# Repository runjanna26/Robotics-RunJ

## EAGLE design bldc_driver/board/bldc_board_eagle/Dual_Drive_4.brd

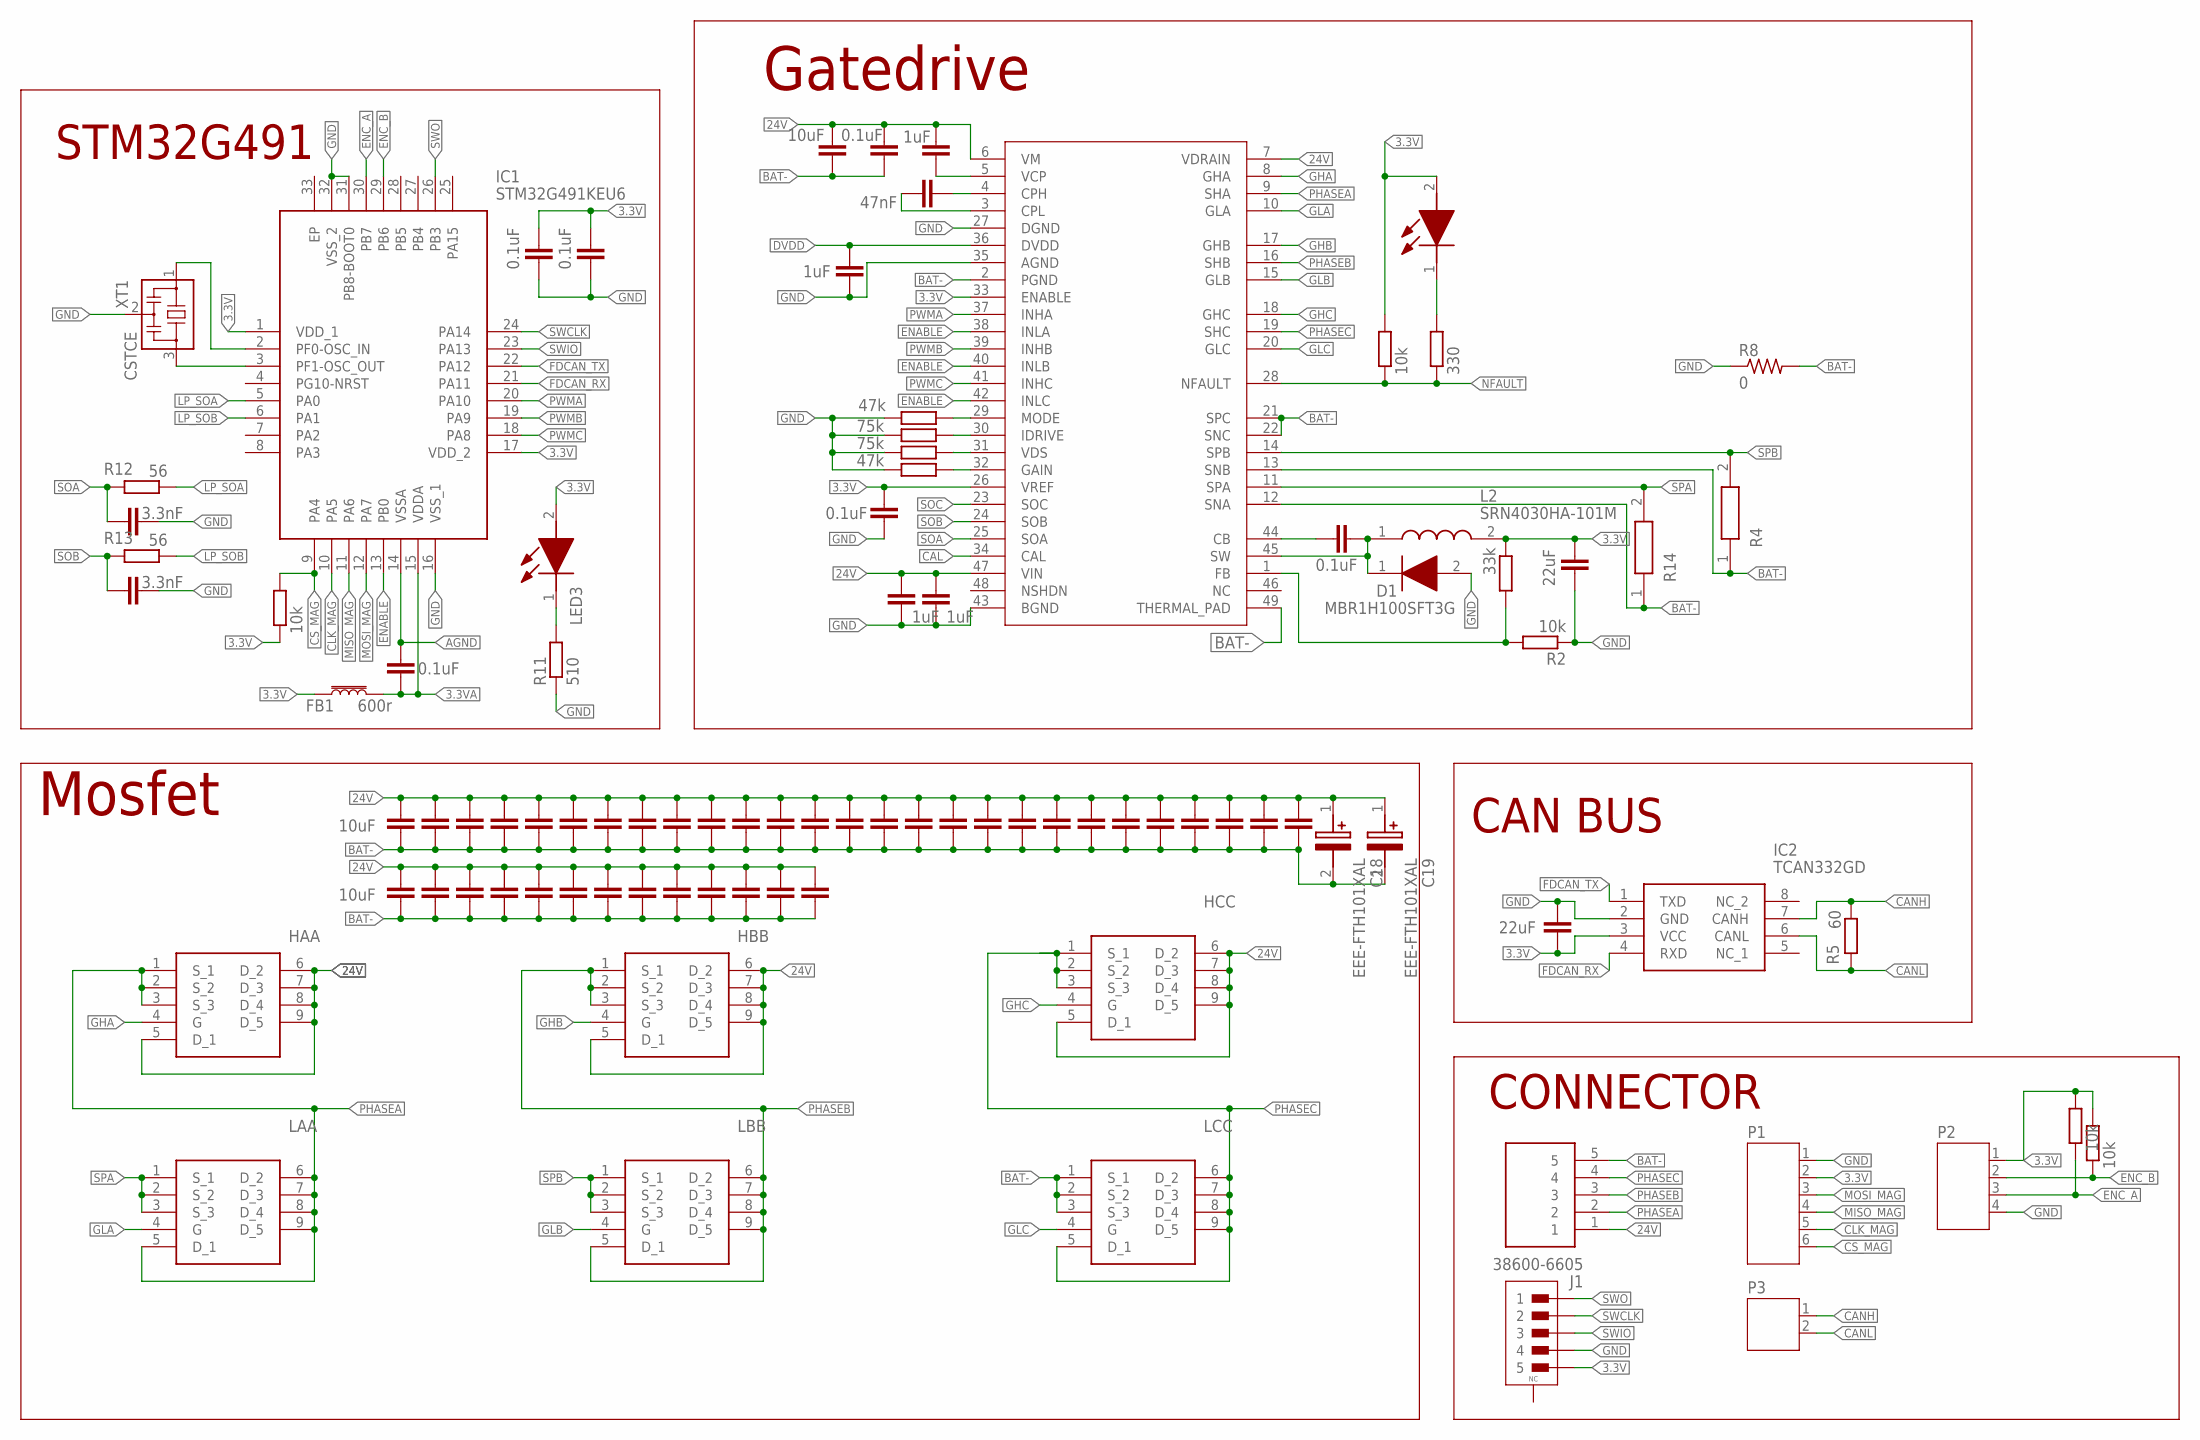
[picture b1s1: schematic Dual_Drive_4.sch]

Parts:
C1, C2: 3.3nF; C0603
C3, C5, C6, C7, C8, C9, C12, C16, C17, C20, C21, C22, C23, C24, C25, C28, C29, C31, C32, C33, C34, C35, C36, C37, C38, C39, C40, C41, C42, C43, C44, C47, C48, C49, C50, C51, C52, C53, C54, C55, C56: 10uF; C1206
C4, C46: 22uF; C0603
C10: 0.1uF; C1206
C11, C14: 1uF; C0603
C13, C15, C26, C27, C30: 0.1uF; C0603
C18, C19: EEE-FTH101XAL; EEEHP1H4R7P
C45: 47nF; C0805
CIN, CIN1: 1uF; C0603
D1: MBR1H100SFT3G; SODFL3616X98N
FB1: 600r; 0603
HAA: TPH2R506PL,L1Q; TPHR9003NLL1Q
HBB: TPH2R506PL,L1Q; TPHR9003NLL1Q
HCC: TPH2R506PL,L1Q; TPHR9003NLL1Q
IC1: STM32G491KEU6; QFN50P500X500X60-33N
IC2: TCAN332GD; SOIC127P600X175-8N
IC3: DRV8323RHRGZR; QFN50P700X700X100-49N
J1: 38600-6605; 386006605
L2: SRN4030HA-101M; SRN4030HA101M
LAA: TPH2R506PL,L1Q; TPHR9003NLL1Q
LBB: TPH2R506PL,L1Q; TPHR9003NLL1Q
LCC: TPH2R506PL,L1Q; TPHR9003NLL1Q
LED1, LED3: LTST-C191KRKT; LEDC1608X55N
P1: JST-PH6
P2: JST-PH4
P3: JST-PH2
R1: 33k; R0603
R2: 10k; R0603
R3, R6: 47k; R0603
R4, R14: 0.01; RESC6434X90N
R5: 60; R0603
R7, R10: 75k; R0603
R8: 0; M1206
R11: 510; R0603
R12, R13: 56; R0603
RPULL, RPULL2, RPULL3, RPULL4: 10k; R0603
RPULL1: 330; R0603
U$3: CON-JST-PH2.0-5PIN-SMD
XT1: CSTCE

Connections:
3.3V: C4.2, C15.1, C26.1, C27.1, C46.1, FB1.1, IC1.1 (VDD_1), IC1.17 (VDD_2), IC2.3 (VCC), IC3.26 (VREF), IC3.33 (ENABLE), L2.2, LED1.2 (A), LED3.2 (A), P1.2, P2.1, R1.2, RPULL.2, RPULL2.1, RPULL3.2, RPULL4.2, U$3.5
3.3VA: C30.1, FB1.2, IC1.15 (VDDA)
24V: C3.1, C5.1, C6.1, C7.1, C8.1, C9.1, C10.1, C11.1, C12.1, C16.1, C17.1, C18.1 (+), C19.1 (+), C20.1, C21.1, C22.1, C23.1, C24.1, C25.1, C28.1, C29.1, C31.1, C32.1, C33.1, C34.1, C35.1, C36.1, C37.1, C38.1, C39.1, C40.1, C41.1, C42.1, C43.1, C44.1, C47.1, C48.1, C49.1, C50.1, C51.1, C52.1, C53.1, C54.1, C55.1, C56.1, CIN.1, CIN1.1, HAA.5 (D_1), HAA.6 (D_2), HAA.7 (D_3), HAA.8 (D_4), HAA.9 (D_5), HBB.5 (D_1), HBB.6 (D_2), HBB.7 (D_3), HBB.8 (D_4), HBB.9 (D_5), HCC.5 (D_1), HCC.6 (D_2), HCC.7 (D_3), HCC.8 (D_4), HCC.9 (D_5), IC3.6 (VM), IC3.7 (VDRAIN), IC3.47 (VIN), J1.1
AGND: C30.2, IC1.14 (VSSA)
BAT-: C3.2, C5.2, C6.2, C7.2, C8.2, C9.2, C10.2, C12.2, C16.2, C17.2, C18.2 (-), C19.2 (-), C20.2, C21.2, C22.2, C23.2, C24.2, C25.2, C28.2, C29.2, C31.2, C32.2, C33.2, C34.2, C35.2, C36.2, C37.2, C38.2, C39.2, C40.2, C41.2, C42.2, C43.2, C44.2, C47.2, C48.2, C49.2, C50.2, C51.2, C52.2, C53.2, C54.2, C55.2, C56.2, IC3.2 (PGND), IC3.12 (SNA), IC3.13 (SNB), IC3.21 (SPC), IC3.22 (SNC), IC3.49 (THERMAL_PAD), J1.5, LCC.1 (S_1), LCC.2 (S_2), LCC.3 (S_3), R4.1, R8.2, R14.1
CAL: IC3.34 (CAL)
CANH: IC2.7 (CANH), P3.1, R5.1
CANL: IC2.6 (CANL), P3.2, R5.2
CB: C13.1, IC3.44 (CB)
CLK_MAG: IC1.10 (PA5), P1.5
CPH: C45.2, IC3.4 (CPH)
CPL: C45.1, IC3.3 (CPL)
CS_MAG: IC1.9 (PA4), P1.6, RPULL2.2
DVDD: C14.1, IC3.36 (DVDD)
ENABLE: IC1.13 (PB0), IC3.38 (INLA), IC3.40 (INLB), IC3.42 (INLC)
ENC_A: IC1.30 (PB7), P2.3, RPULL4.1
ENC_B: IC1.29 (PB6), P2.2, RPULL3.1
FB: IC3.1 (FB), R1.1, R2.2
FDCAN_RX: IC1.21 (PA11), IC2.4 (RXD)
FDCAN_TX: IC1.22 (PA12), IC2.1 (TXD)
GAIN: IC3.32 (GAIN), R3.2
GHA: HAA.4 (G), IC3.8 (GHA)
GHB: HBB.4 (G), IC3.17 (GHB)
GHC: HCC.4 (G), IC3.18 (GHC)
GLA: IC3.10 (GLA), LAA.4 (G)
GLB: IC3.15 (GLB), LBB.4 (G)
GLC: IC3.20 (GLC), LCC.4 (G)
GND: C1.2, C2.2, C4.1, C14.2, C15.2, C26.2, C27.2, C46.2, CIN.2, CIN1.2, D1.2 (A), IC1.16 (VSS_1), IC1.31 (PB8-BOOT0), IC1.32 (VSS_2), IC2.2 (GND), IC3.27 (DGND), IC3.35 (AGND), IC3.43 (BGND), P1.1, P2.4, R2.1, R3.1, R6.1, R7.1, R8.1, R10.1, R11.1, U$3.4, XT1.2
IDRIVE: IC3.30 (IDRIVE), R7.2
LEDFAULT: LED1.1 (K), RPULL1.2
LP_SOA: IC1.5 (PA0), R12.1
LP_SOB: IC1.6 (PA1), R13.1
MISO_MAG: IC1.11 (PA6), P1.4
MODE: IC3.29 (MODE), R6.2
MOSI_MAG: IC1.12 (PA7), P1.3
unnamed: IC1.3 (PF1-OSC_OUT), XT1.3
unnamed: LED3.1 (K), R11.2
unnamed: IC1.2 (PF0-OSC_IN), XT1.1
NFAULT: IC3.28 (NFAULT), RPULL.1, RPULL1.1
PHASEA: HAA.1 (S_1), HAA.2 (S_2), HAA.3 (S_3), IC3.9 (SHA), J1.2, LAA.5 (D_1), LAA.6 (D_2), LAA.7 (D_3), LAA.8 (D_4), LAA.9 (D_5)
PHASEB: HBB.1 (S_1), HBB.2 (S_2), HBB.3 (S_3), IC3.16 (SHB), J1.3, LBB.5 (D_1), LBB.6 (D_2), LBB.7 (D_3), LBB.8 (D_4), LBB.9 (D_5)
PHASEC: HCC.1 (S_1), HCC.2 (S_2), HCC.3 (S_3), IC3.19 (SHC), J1.4, LCC.5 (D_1), LCC.6 (D_2), LCC.7 (D_3), LCC.8 (D_4), LCC.9 (D_5)
PWMA: IC1.20 (PA10), IC3.37 (INHA)
PWMB: IC1.19 (PA9), IC3.39 (INHB)
PWMC: IC1.18 (PA8), IC3.41 (INHC)
SOA: C1.1, IC3.25 (SOA), R12.2
SOB: C2.1, IC3.24 (SOB), R13.2
SOC: IC3.23 (SOC)
SPA: IC3.11 (SPA), LAA.1 (S_1), LAA.2 (S_2), LAA.3 (S_3), R14.2
SPB: IC3.14 (SPB), LBB.1 (S_1), LBB.2 (S_2), LBB.3 (S_3), R4.2
SW: C13.2, D1.1 (K), IC3.45 (SW), L2.1
SWCLK: IC1.24 (PA14), U$3.2
SWIO: IC1.23 (PA13), U$3.3
SWO: IC1.26 (PB3), U$3.1
VCP: C11.2, IC3.5 (VCP)
VDS: IC3.31 (VDS), R10.2

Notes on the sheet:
Mosfet
CONNECTOR
STM32G491
CAN BUS
Gatedrive

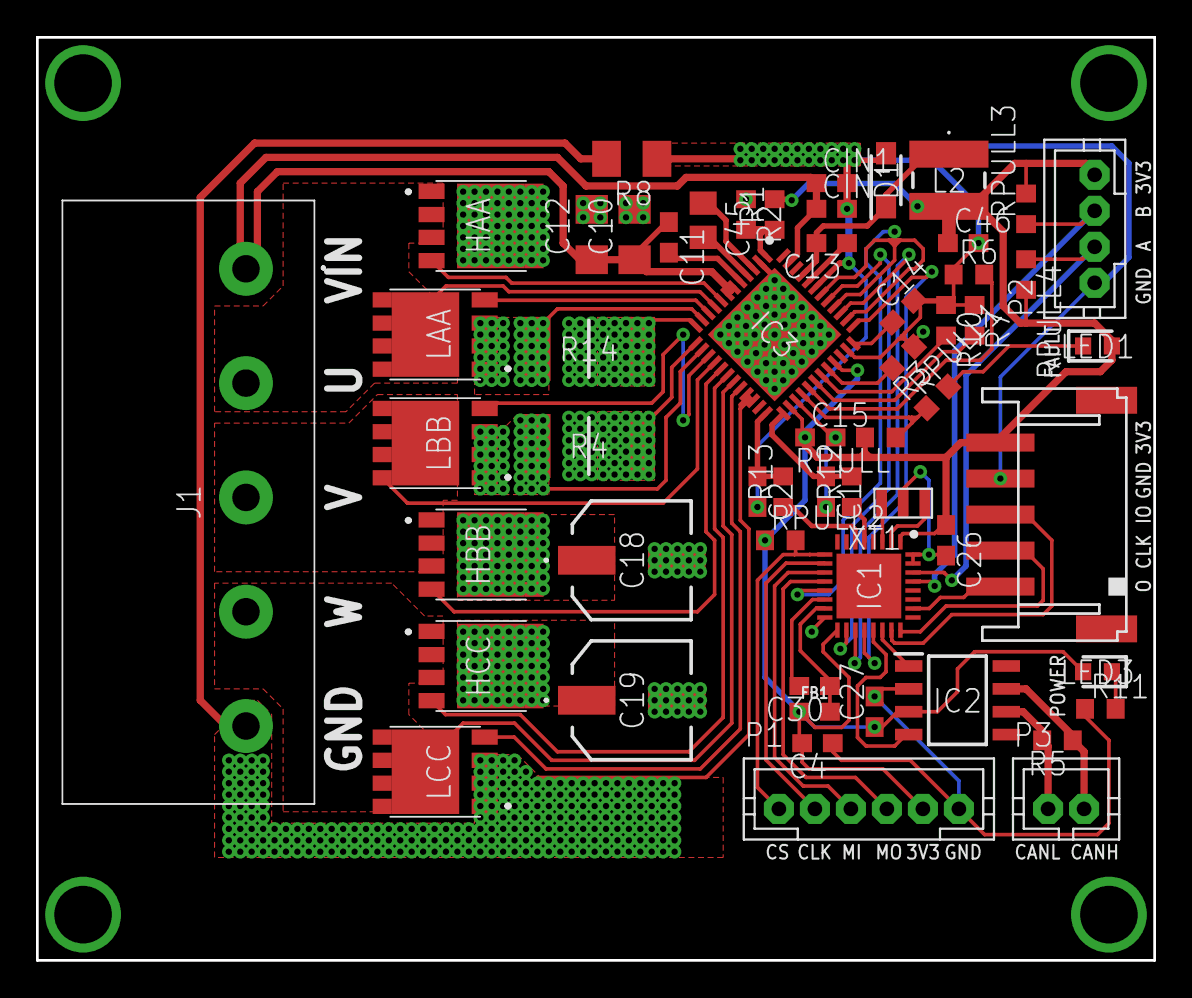
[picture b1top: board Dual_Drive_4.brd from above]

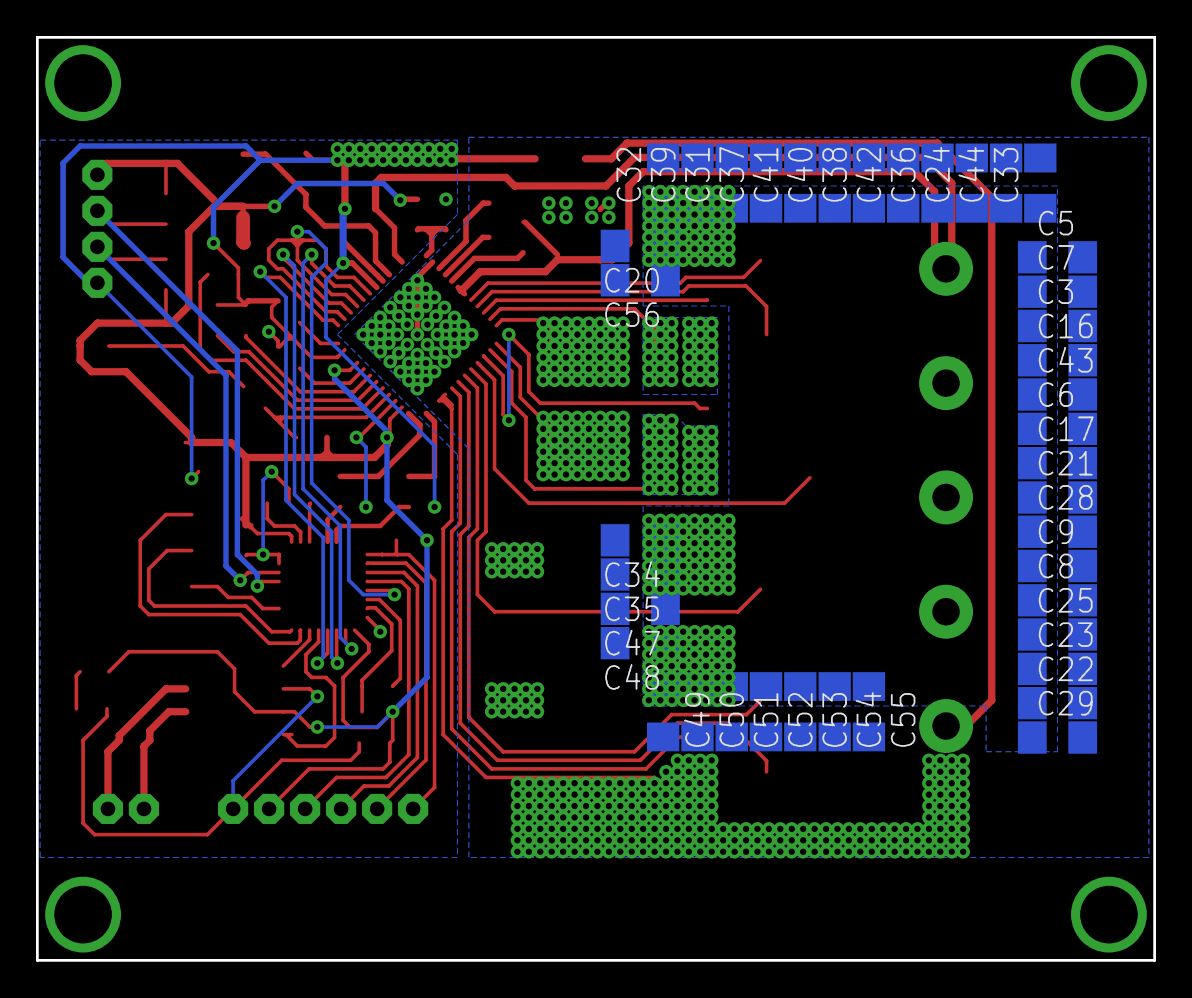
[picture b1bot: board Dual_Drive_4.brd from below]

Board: 2 copper layers, 62.1 x 51.3 mm, 96 parts (40 on the bottom side), 54 nets.

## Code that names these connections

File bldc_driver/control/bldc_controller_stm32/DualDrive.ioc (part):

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Mcu.Name=STM32G491K(C-E)Ux
Mcu.Package=UFQFPN32
Mcu.UserName=STM32G491KEUx
PA0.GPIOParameters=GPIO_Label
PA0.GPIO_Label=CSOA
PA0.Mode=IN1-Single-Ended
PA0.Signal=ADC1_IN1
PA1.GPIOParameters=GPIO_Label
PA1.GPIO_Label=CSOB
PA1.Mode=IN2-Single-Ended
PA1.Signal=ADC2_IN2
PA10.GPIOParameters=GPIO_Speed,GPIO_Label
PA10.GPIO_Label=PWMA
PA10.GPIO_Speed=GPIO_SPEED_FREQ_VERY_HIGH
PA10.Signal=S_TIM1_CH3
PA11.Mode=FDCAN_Activate
PA11.Signal=FDCAN1_RX
PA12.Mode=FDCAN_Activate
PA12.Signal=FDCAN1_TX
PA13.Mode=Serial_Wire
PA13.Signal=SYS_JTMS-SWDIO
PA14.Mode=Serial_Wire
PA14.Signal=SYS_JTCK-SWCLK
PA15.GPIOParameters=GPIO_Label
PA15.GPIO_Label=ENABLE
PA15.Signal=GPIO_Output
PA4.GPIOParameters=GPIO_Label
PA4.GPIO_Label=CS_CON
PA4.Signal=GPIO_Output
PA5.GPIOParameters=GPIO_Speed,GPIO_Label
PA5.GPIO_Label=CLK_CON
PA5.GPIO_Speed=GPIO_SPEED_FREQ_LOW
PA5.Mode=Full_Duplex_Master
PA5.Signal=SPI1_SCK
PA6.GPIOParameters=GPIO_Speed,GPIO_Label
PA6.GPIO_Label=MISO_CON
PA6.GPIO_Speed=GPIO_SPEED_FREQ_LOW
PA6.Mode=Full_Duplex_Master
PA6.Signal=SPI1_MISO
PA7.GPIOParameters=GPIO_Speed,GPIO_Label
PA7.GPIO_Label=MOSI_CON
PA7.GPIO_Speed=GPIO_SPEED_FREQ_LOW
PA7.Mode=Full_Duplex_Master
PA7.Signal=SPI1_MOSI
PA8.GPIOParameters=GPIO_Speed,GPIO_Label
PA8.GPIO_Label=PWMC
PA8.GPIO_Speed=GPIO_SPEED_FREQ_VERY_HIGH
PA8.Signal=S_TIM1_CH1
PA9.GPIOParameters=GPIO_Speed,GPIO_Label
PA9.GPIO_Label=PWMB
PA9.GPIO_Speed=GPIO_SPEED_FREQ_VERY_HIGH
PA9.Signal=S_TIM1_CH2
PB0.GPIOParameters=GPIO_Label
PB0.GPIO_Label=ENABLE
PB0.Signal=GPIO_Output
PB6.Signal=S_TIM4_CH1
PB7.Signal=S_TIM4_CH2
PF0-OSC_IN.Mode=HSE-External-Oscillator
PF0-OSC_IN.Signal=RCC_OSC_IN
PF1-OSC_OUT.Mode=HSE-External-Oscillator
PF1-OSC_OUT.Signal=RCC_OSC_OUT
RCC.HSE_VALUE=8000000
RCC.SYSCLKFreq_VALUE=170000000
RCC.SYSCLKSource=RCC_SYSCLKSOURCE_PLLCLK
board=custom

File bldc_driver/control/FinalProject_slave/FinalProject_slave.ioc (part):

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Mcu.Name=STM32F103C(8-B)Tx
Mcu.Package=LQFP48
Mcu.UserName=STM32F103C8Tx
PA0-WKUP.GPIOParameters=GPIO_Label
PA0-WKUP.GPIO_Label=PWMA
PA0-WKUP.Signal=S_TIM2_CH1_ETR
PA1.GPIOParameters=GPIO_Label
PA1.GPIO_Label=PWMB
PA1.Signal=S_TIM2_CH2
PA10.Mode=Asynchronous
PA10.Signal=USART1_RX
PA11.Mode=CAN_Activate
PA11.Signal=CAN_RX
PA12.Mode=CAN_Activate
PA12.Signal=CAN_TX
PA13.Mode=Serial_Wire
PA13.Signal=SYS_JTMS-SWDIO
PA14.Mode=Serial_Wire
PA14.Signal=SYS_JTCK-SWCLK
PA2.GPIOParameters=GPIO_Label
PA2.GPIO_Label=PWMC
PA2.Signal=S_TIM2_CH3
PA3.GPIOParameters=GPIO_Label
PA3.GPIO_Label=SOA
PA3.Signal=ADCx_IN3
PA4.GPIOParameters=GPIO_Label
PA4.GPIO_Label=SPI1_NSS
PA4.Signal=GPIO_Output
PA5.Mode=Full_Duplex_Master
PA5.Signal=SPI1_SCK
PA6.Mode=Full_Duplex_Master
PA6.Signal=SPI1_MISO
PA7.Mode=Full_Duplex_Master
PA7.Signal=SPI1_MOSI
PA9.Mode=Asynchronous
PA9.Signal=USART1_TX
PB0.GPIOParameters=GPIO_Label
PB0.GPIO_Label=SOB
PB0.Signal=ADCx_IN8
PB1.GPIOParameters=GPIO_Label
PB1.GPIO_Label=SOC
PB1.Signal=ADCx_IN9
PB12.Signal=GPIO_Output
PB5.GPIOParameters=GPIO_Label
PB5.GPIO_Label=EN
PB5.Signal=GPIO_Output
PC13-TAMPER-RTC.Signal=GPIO_Output
PD0-OSC_IN.Mode=HSE-External-Oscillator
PD0-OSC_IN.Signal=RCC_OSC_IN
PD1-OSC_OUT.Mode=HSE-External-Oscillator
PD1-OSC_OUT.Signal=RCC_OSC_OUT
RCC.SYSCLKFreq_VALUE=72000000
RCC.SYSCLKSource=RCC_SYSCLKSOURCE_PLLCLK
board=custom

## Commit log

2023-06-11 Update FK IK Jacobian
2023-06-12 HERO-H4 FK
2023-06-12 update H4 FK
2023-06-13 Updated: transformation matrix of Folk
2023-06-13 commit the changed
2023-06-13 'add jaco arm kinematic and 3Dplot'
2023-06-13 update py JACO arm
2023-06-14 update plot3D completed
2023-06-14 update init pos
2023-06-14 Rearrange files
2023-06-15 update jacobian of JACO arm into function
2023-07-04 update OpenManipulator FK
2024-05-04 update new project BLDC driver, jaco arm simscape and rearrage folder
2024-05-06 update PCB
2024-05-08 update PCB BLDC Driver [Done]
2024-05-09 update for PCB ver 2
2024-05-09 update board ver 2
2024-05-10 Finish the BLDC board drive ver.2
2024-05-11 minor update
2024-05-11 update board v2
2024-05-18 add project eiei for re-writing the structure
2024-05-18 for pulling
2024-05-18 push gitignore
2024-05-18 update class of simpleFOC
2024-05-20 update online
2024-05-20 update Fully simpleFOC [Done]
2024-05-30 update latest control to new board by runj!!
2024-05-31 update PWM done/ Encoder done/
2024-06-02 update can do closed loop control Done !! but still not tuning yet
2024-06-02 update EKF velocity esitmation
2024-06-03 update CORDIC
2024-06-04 update EKF modular
2024-06-07 update latest code
2024-10-31 pull
2024-11-24 update dmps for learning modules
2024-11-24 update CPG-RBF
2024-11-24 update online gait cycle detector
2024-11-25 update gait cycle imiatation
2024-11-26 update code
2024-11-29 update cpg rbf
2024-11-29 plot error
2024-11-29 update json
2024-12-01 update evolution plot
2024-12-02 update to merge
2024-12-02 update plot weight/error 3D graph
2024-12-04 commit to merge
2024-12-09 update adapt path from muscle error
2024-12-12 merge
2024-12-24 update can commu for bldc controller
2024-12-24 update can interface for bldc controller
2024-12-24 update can bus module for bldc
2025-01-01 update CAN full communication: Done
2025-01-19 update tuning motor's parameters: Done
2025-01-21 update mujoco simulation
2025-01-22 update swerve wheel module
2025-02-02 update magnet wheel sim and marine sim
2025-02-15 update sanpoom test
2025-02-19 update stick insect simulation
2025-02-23 update sim stick insect real path
2025-02-24 update save files
2025-04-27 update esp32s3 project into this repo
2025-04-27 Update submodule URL and add project files
2025-04-27 Add micro-ROS ESP-IDF component submodule
2025-04-27 complete esp32s3 project which can work with micro-ros
2025-06-29 update esp32s3 project with uROS
2025-06-29 rename project
2025-07-30 update encoder
2025-08-04 update dynamixel sdk into project
2025-08-05 update esp32_project with dynamixel DONE
2025-08-05 Rename LITHE joint folder
2025-08-08 update esp32s3 for helical joint experiment
2025-08-08 clean esp32s3 project and duplicate file for helic joint experiment
2025-08-20 update bending experiment code
2025-08-20 compression tension code experiment
2025-10-07 update RMD motor control with CAN
2025-10-08 update test uros topic and msg reading motor feedback
2025-10-29 update esp32-s3 project: muscle + station receive command
2025-11-03 update esp32-s3 project: update cpg pause and rewind

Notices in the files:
parts and their libraries:
SparkFun-Coils: Licensing: Creative Commons ShareAlike 4.0 International - https://creativecommons.org/licenses/by-sa/4.0
